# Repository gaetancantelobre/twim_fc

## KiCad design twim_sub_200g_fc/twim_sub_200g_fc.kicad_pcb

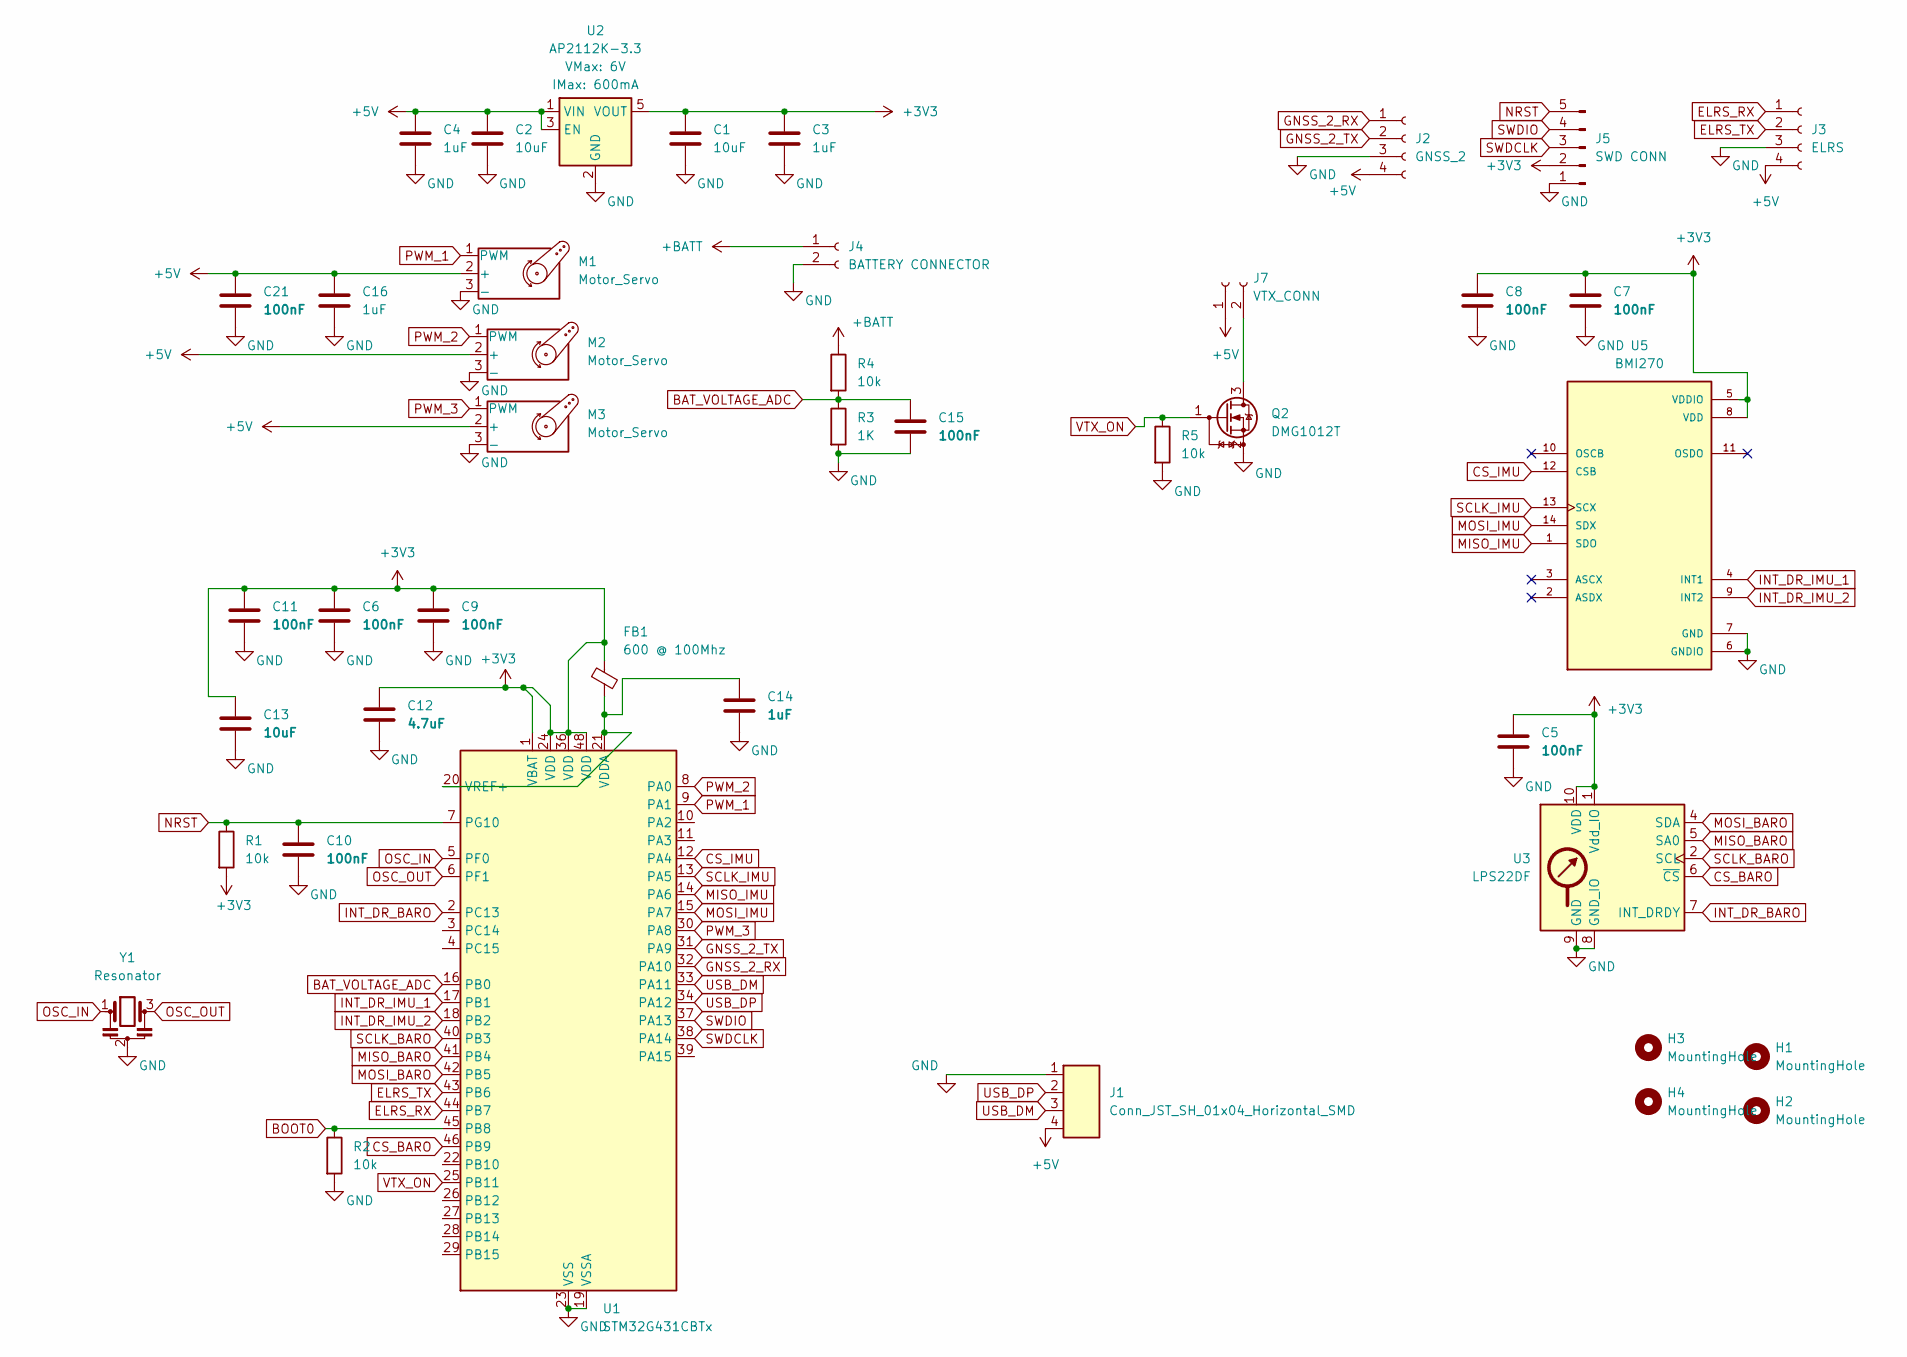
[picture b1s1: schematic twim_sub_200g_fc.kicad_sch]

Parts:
C1, C2, C13: 10uF; C_0603_1608Metric
C3, C4, C14, C16: 1uF; C_0402_1005Metric
C5, C6, C7, C8, C9, C10, C11, C15, C21: 100nF; C_0402_1005Metric
C12: 4.7uF; C_0603_1608Metric
FB1: 600 @ 100Mhz; L_0402_1005Metric
H1, H2, H3, H4: MountingHole; MountingHole_2.2mm_M2
J1: Conn_JST_SH_01x04_Horizontal_SMD
J2: GNSS_2; 01x04_smd_pad_1.2mm
J3: ELRS; 01x04_smd_pad_1.2mm
J4: BATTERY CONNECTOR; 01x02_smd_pad_1.2mm
J5: SWD CONN; Molex_PicoBlade_53047-0510_1x05_P1.25mm_Vertical
J7: VTX_CONN; 01x02_smd_pad_1.2mm
M1, M2, M3: Motor_Servo; PinHeader_1x03_P2.54mm_Vertical
Q2: DMG1012T; SOT-523
R1, R2, R4, R5: 10k; R_0402_1005Metric
R3: 1K; R_0402_1005Metric
U1: STM32G431CBTx; LQFP-48_7x7mm_P0.5mm
U2: AP2112K-3.3; SOT23-5
U3: LPS22DF; ST_HLGA-10_2x2mm_P0.5mm_LayoutBorder3x2y
U5: BMI270; XDCR_BMI270
Y1: Resonator; Resonator_SMD_Murata_CSTxExxV-3Pin_3.0x1.1mm

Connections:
+3V3: C1.1, C3.1, C5.1, C6.1, C7.1, C8.1, C9.1, C11.1, C12.1, C13.1, FB1.1, J5.2, R1.2, U1.1 (VBAT), U1.24 (VDD), U1.36 (VDD), U1.48 (VDD), U2.5 (VOUT), U3.1 (Vdd_IO), U3.10 (VDD), U5.5 (VDDIO), U5.8 (VDD); also elsewhere on the board
+5V: C2.1, C4.1, C16.1, C21.1, J1.4, J2.4, J3.4, J7.1, M1.2 (+), M2.2 (+), M3.2 (+), U2.1 (VIN), U2.3 (EN); also elsewhere on the board
+BATT: J4.1, R4.1
BAT_VOLTAGE_ADC: C15.1, R3.1, R4.2, U1.16 (PB0)
BOOT0: R2.1, U1.45 (PB8)
CS_BARO: U1.46 (PB9), U3.6 (~CS)
CS_IMU: U1.12 (PA4), U5.12 (CSB)
ELRS_RX: J3.1, U1.44 (PB7)
ELRS_TX: J3.2, U1.43 (PB6)
GND: C1.2, C2.2, C3.2, C4.2, C5.2, C6.2, C7.2, C8.2, C9.2, C10.2, C11.2, C12.2, C13.2, C14.2, C15.2, C16.2, C21.2, J1.1, J2.3, J3.3, J4.2, J5.1, M1.3 (-), M2.3 (-), M3.3 (-), Q2.2 (S), R2.2, R3.2, R5.2, U1.19 (VSSA), U1.23 (VSS), U1.35 (VSS), U1.47 (VSS), U2.2 (GND), U3.3 (GND), U3.8 (GND_IO), U3.9 (GND), U5.6 (GNDIO), U5.7 (GND), Y1.2; also elsewhere on the board
GNSS_2_RX: J2.1, U1.32 (PA10)
GNSS_2_TX: J2.2, U1.31 (PA9)
INT_DR_BARO: U1.2 (PC13), U3.7 (INT_DRDY)
INT_DR_IMU_1: U1.17 (PB1), U5.4 (INT1)
INT_DR_IMU_2: U1.18 (PB2), U5.9 (INT2)
MISO_BARO: U1.41 (PB4), U3.5 (SA0)
MISO_IMU: U1.14 (PA6), U5.1 (SDO)
MOSI_BARO: U1.42 (PB5), U3.4 (SDA)
MOSI_IMU: U1.15 (PA7), U5.14 (SDX)
NRST: C10.1, J5.5, R1.1, U1.7 (PG10)
unnamed: J7.2, Q2.3 (D)
unnamed: C14.1, FB1.2, U1.20 (VREF+), U1.21 (VDDA)
OSC_IN: U1.5 (PF0), Y1.1
OSC_OUT: U1.6 (PF1), Y1.3
PWM_1: M1.1 (PWM), U1.9 (PA1)
PWM_2: M2.1 (PWM), U1.8 (PA0)
PWM_3: M3.1 (PWM), U1.30 (PA8)
SCLK_BARO: U1.40 (PB3), U3.2 (SCL)
SCLK_IMU: U1.13 (PA5), U5.13 (SCX)
SWDCLK: J5.3, U1.38 (PA14)
SWDIO: J5.4, U1.37 (PA13)
USB_DM: J1.3, U1.33 (PA11)
USB_DP: J1.2, U1.34 (PA12)
VTX_ON: Q2.1 (G), R5.1, U1.25 (PB11)

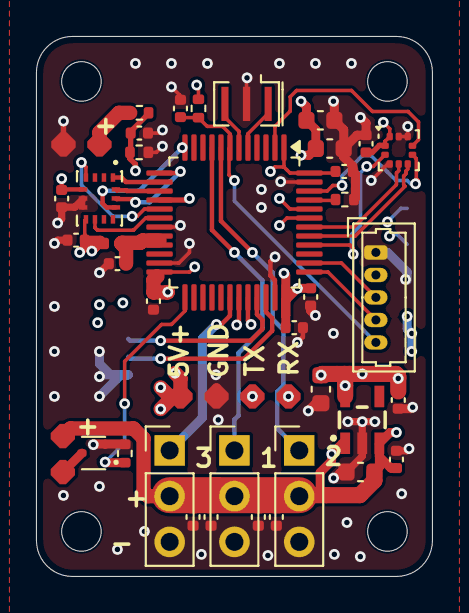
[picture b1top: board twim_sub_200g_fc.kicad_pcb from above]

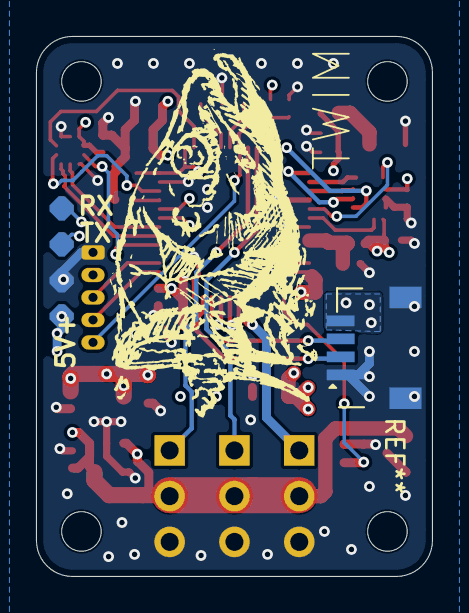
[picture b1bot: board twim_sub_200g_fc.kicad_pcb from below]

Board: 4 copper layers, 22.0 x 30.0 mm, 45 parts (2 on the bottom side), 34 nets.

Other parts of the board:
C6#2, C21#2: 100nF; C_0402_1005Metric
C16#2: 1uF; C_0402_1005Metric

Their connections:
+3V3: C6#2.1; also elsewhere on the board
+5V: C16#2.1, C21#2.1; also elsewhere on the board
GND: C6#2.2, C16#2.2, C21#2.2; also elsewhere on the board

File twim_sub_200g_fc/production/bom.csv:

Designator,Footprint,Quantity,Value,LCSC Part #
"C1, C13, C2",0603,3,10uF,
"C10, C11, C15, C21_2, C21, C5, C6_2, C6, C7, C8, C9",0402,11,100nF,
C12,0603,1,4.7uF,
"C14, C16_2, C16, C3, C4",0402,5,1uF,
FB1,0402,1,600 @ 100Mhz,
J1,Conn_JST_SH_01x04_Horizontal_SMD,1,Conn_JST_SH_01x04_Horizontal_SMD,
J2,01x04_smd_pad_1.2mm,1,GNSS_2,
J3,01x04_smd_pad_1.2mm,1,ELRS,
J4,01x02_smd_pad_1.2mm,1,BATTERY CONNECTOR,
J5,Molex_PicoBlade_53047-0510_1x05_P1.25mm_Vertical,1,SWD CONN,
J7,01x02_smd_pad_1.2mm,1,VTX_CONN,
"M1, M2, M3",PinHeader_1x03_P2.54mm_Vertical,3,Motor_Servo,
Q2,SOT-523,1,DMG1012T,
"R1, R2, R4, R5",0402,4,10k,
R3,0402,1,1K,
U1,LQFP-48_7x7mm_P0.5mm,1,STM32G431CBTx,
U2,SOT23-5,1,AP2112K-3.3,
U3,ST_HLGA-10_2x2mm_P0.5mm_LayoutBorder3x2y,1,LPS22DF,
U5,XDCR_BMI270,1,BMI270,
Y1,Resonator_SMD_Murata_CSTxExxV-3Pin_3.0x1.1mm,1,Resonator,

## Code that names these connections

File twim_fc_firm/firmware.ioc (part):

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Mcu.Name=STM32G431C(6-8-B)Tx
Mcu.Package=LQFP48
Mcu.UserName=STM32G431CBTx
PA0.Signal=S_TIM2_CH1
PA1.Signal=S_TIM2_CH2
PA10.Mode=Asynchronous
PA10.Signal=USART1_RX
PA11.Mode=Device
PA11.Signal=USB_DM
PA12.Mode=Device
PA12.Signal=USB_DP
PA13.Signal=SYS_JTMS-SWDIO
PA14.Signal=SYS_JTCK-SWCLK
PA4.Signal=GPIO_Output
PA5.Mode=Full_Duplex_Master
PA5.Signal=SPI1_SCK
PA6.Mode=Full_Duplex_Master
PA6.Signal=SPI1_MISO
PA7.Mode=Full_Duplex_Master
PA7.Signal=SPI1_MOSI
PA8.Signal=S_TIM1_CH1
PA9.Mode=Asynchronous
PA9.Signal=USART1_TX
PB0.Signal=ADC1_IN15
PB1.Signal=GPIO_Input
PB11.Signal=GPIO_Output
PB2.Signal=GPIO_Input
PB3.Mode=Full_Duplex_Master
PB3.Signal=SPI3_SCK
PB4.Mode=Full_Duplex_Master
PB4.Signal=SPI3_MISO
PB5.Mode=Full_Duplex_Master
PB5.Signal=SPI3_MOSI
PB9.Signal=GPIO_Output
PC13.Signal=GPIO_Input
PF0-OSC_IN.Mode=HSE-External-Oscillator
PF0-OSC_IN.Signal=RCC_OSC_IN
PF1-OSC_OUT.Mode=HSE-External-Oscillator
PF1-OSC_OUT.Signal=RCC_OSC_OUT
RCC.HSE_VALUE=8000000
RCC.SYSCLKFreq_VALUE=16000000
board=custom

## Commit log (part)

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2026-06-10 added basis for 90g delta wing
2026-06-11 qsss
2026-06-14 added main layout 22mmx30mm
2026-06-14 added baselayout
2026-06-17 adddd
2026-06-17 adadad
2026-06-19 added tom's changes
2026-06-21 finished V1
